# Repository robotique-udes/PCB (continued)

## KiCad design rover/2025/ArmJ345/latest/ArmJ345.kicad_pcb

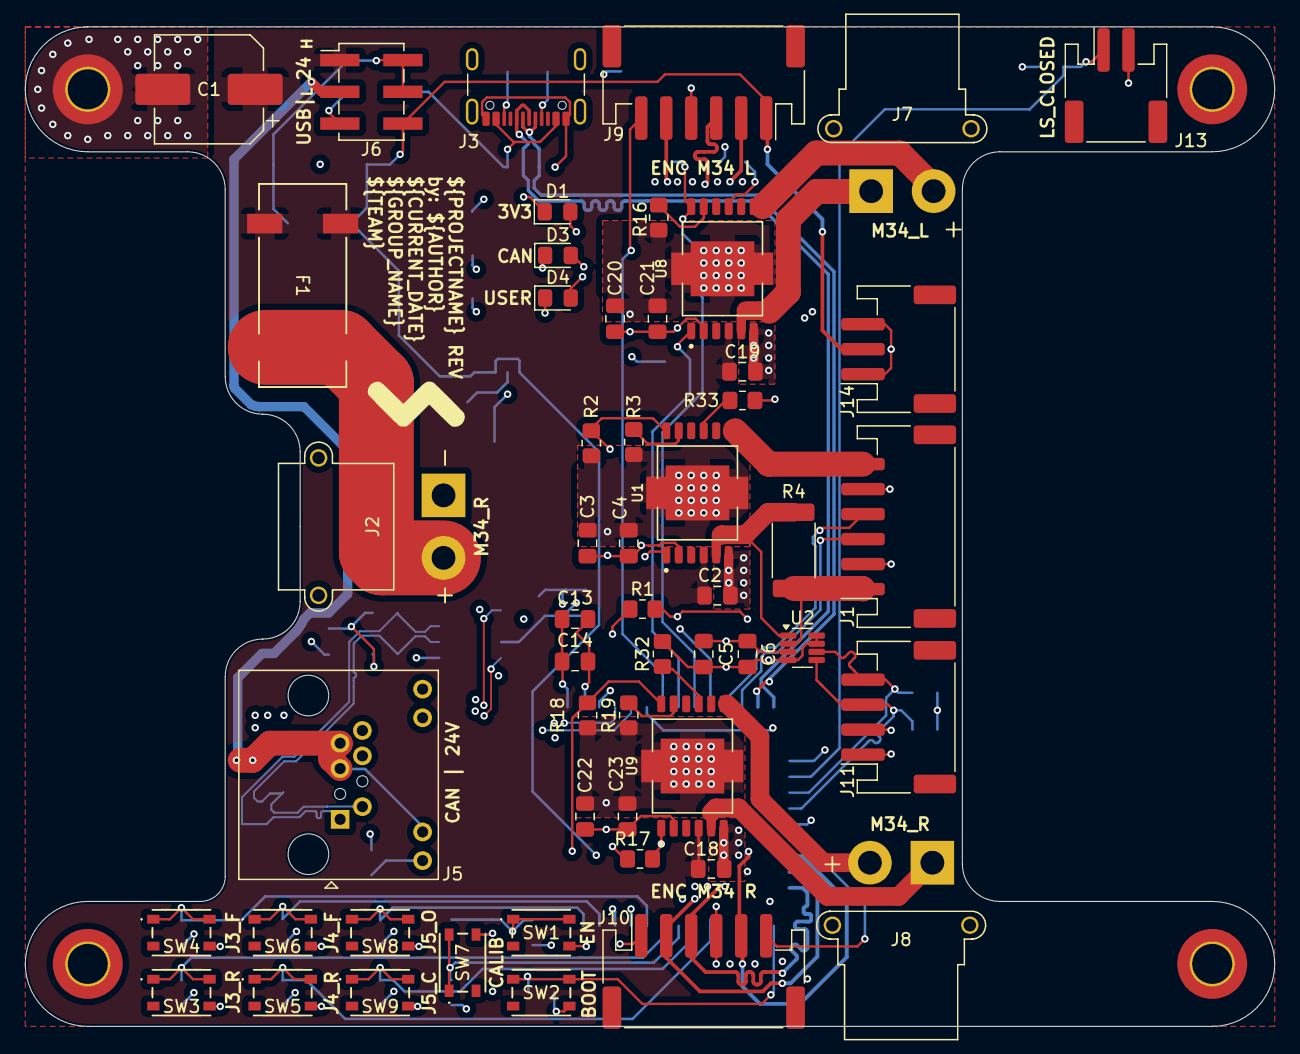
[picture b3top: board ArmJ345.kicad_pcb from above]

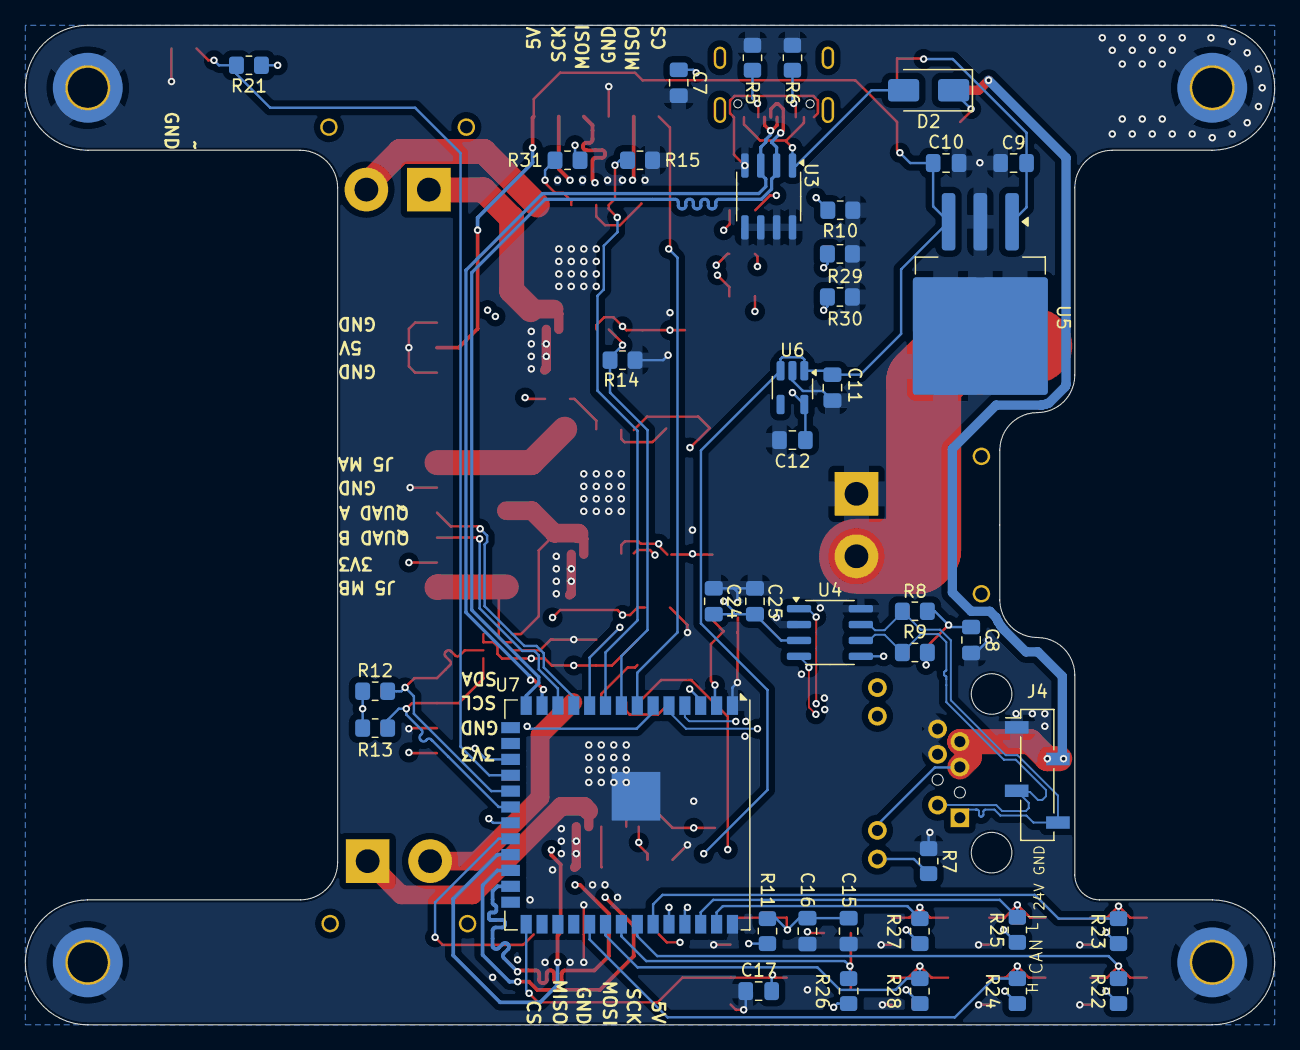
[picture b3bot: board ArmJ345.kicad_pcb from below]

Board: 4 copper layers, 100.0 x 80.0 mm, 97 parts (40 on the bottom side), 63 nets.

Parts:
C1: 470uF; CP_Elec_8x10.5
C2, C4, C6, C14, C16, C17, C18, C19, C21, C23, C25: 100nF; C_0805_2012Metric_Pad1.18x1.45mm_HandSolder
C3, C5, C9, C10, C11, C12, C13, C20, C22, C24: 10uF; C_0805_2012Metric_Pad1.18x1.45mm_HandSolder
C7: 1nF; C_0805_2012Metric_Pad1.18x1.45mm_HandSolder
C8: 4.7nF; C_0805_2012Metric_Pad1.18x1.45mm_HandSolder
C15: 1uF; C_0805_2012Metric_Pad1.18x1.45mm_HandSolder
D1: G; LED_0805_2012Metric_Pad1.15x1.40mm_HandSolder
D2: 40V; D_SMA
D3, D4: B; LED_0805_2012Metric_Pad1.15x1.40mm_HandSolder
F1: 15A; FuseHolder-3588-20
H1, H2, H3, H4: MountingHole_Pad; MountingHole_3.2mm_M3_DIN965_Pad_TopBottom
J1: JST_PH_SB6; JST_PH_S6B-PH-SM4-TB_1x06-1MP_P2.00mm_Horizontal
J2: XT30PW-M; AMASS_XT30PW-M_1x02_P2.50mm_Horizontal
J3: USB_C_USB4105-GF-A; USB_C_Receptacle_GCT_USB4105-xx-A_16P_TopMnt_Horizontal
J4: Conn_01x04_Socket; PinSocket_1x04_P2.54mm_Vertical_SMD_Pin1Left
J5: ETH-RJHSE5081
J6: Conn_02x03_Odd_Even; PinHeader_2x03_P2.54mm_Vertical_SMD
J7, J8: XT30PW-M; AMASS_XT30PW-F_1x02_P2.50mm_Horizontal
J9, J10: JST-PH-S6B; JST_PH_S6B-PH-SM4-TB_1x06-1MP_P2.00mm_Horizontal
J11: Conn_01x04_MountingPin; JST_PH_S4B-PH-SM4-TB_1x04-1MP_P2.00mm_Horizontal
J13: Conn_01x02_MountingPin; JST_PH_S2B-PH-SM4-TB_1x02-1MP_P2.00mm_Horizontal
J14: Conn_01x03_MountingPin; JST_PH_S3B-PH-SM4-TB_1x03-1MP_P2.00mm_Horizontal
R1, R2, R3, R11, R14, R15, R16, R17, R18, R19, R21, R22, R23, R24, R25, R26, R27, R28, R31, R32, R33: 10k; R_0805_2012Metric_Pad1.20x1.40mm_HandSolder
R4: 0.05 (CRA2512-FZ-R050ELF); R_2512_6332Metric_Pad1.40x3.35mm_HandSolder
R5, R6, R7, R10, R29, R30: 5.1k; R_0805_2012Metric_Pad1.20x1.40mm_HandSolder
R8, R9: 60.4; R_0805_2012Metric_Pad1.20x1.40mm_HandSolder
R12, R13: 4.7k; R_0805_2012Metric_Pad1.20x1.40mm_HandSolder
SW1, SW2, SW3, SW4, SW5, SW6, SW7, SW8, SW9: SW-PTS815SJM250SMTRLFS; SW-PTS815 SJM250SMTRLFS
U1, U8, U9: IFX9201SGAUMA1; DRIVE_IFX9201SGAUMA1
U2: CURR_SENSE-INA219AIDCNTG4; SOT-23-8
U3: TVS-SMDB03CE3; SOIC-8_3.9x4.9mm_P1.27mm
U4: SN65HVD232; SOIC-8_3.9x4.9mm_P1.27mm
U5: LDO-LM340SX-5.0/NOPB; TO-263-3_TabPin2
U6: LDO-TLV74033PDBVR; SOT-23-5_HandSoldering
U7: ESP32-S3-WROVER; ESP32-S3-WROOM-1U

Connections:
+3.3V: C3.1, C4.1, C5.1, C6.1, C12.1, C13.1, C14.1, C20.1, C21.1, C22.1, C23.1, C24.1, C25.1, D1.2 (A), J1.2, J11.1, R11.1, R12.1, R13.1, R21.1, R22.1, R23.1, R24.1, R25.1, R26.1, R27.1, R28.1, R31.1, R32.1, R33.1, U1.2 (VSO), U2.4 (VS), U2.7 (A0), U2.8 (A1), U4.3 (VCC), U4.5 (VREF), U6.5 (OUTPUT), U7.2 (3V3), U8.2 (VSO), U9.2 (VSO)
+5V: C10.1, C11.1, J6.6, J9.1, J10.1, J14.2, U5.3 (OUTPUT), U6.1 (INPUT), U6.3 (EN)
+5V_USB: D2.2 (A), J3.A4 (VBUS), J3.A9 (VBUS), J3.B4 (VBUS), J3.B9 (VBUS), U3.1
+24V: C9.1, J6.2, J6.4, U5.1 (INPUT)
+24V_H: C1.1, C2.1, C18.1, C19.1, F1.1, J6.1, U1.4 (VS), U8.4 (VS), U9.4 (VS)
+24V_L: J4.2, J5.5 (Vcc), J5.7 (Vcc), J5.10 (G_L+), J6.3
/Board/drive_j5/M5_A: J1.6, U1.7 (OUT2)
/Board/drive_j5/M5_B: J1.1, R4.2, U2.2 (IN-)
/Board/drive_j5/SENSE_+: R4.1, U1.5 (OUT1), U2.1 (IN+)
/Board/esp32/BOOT_PB: C17.2, SW2.1, SW2.2, U7.27 (IO0-BOOT)
/Board/esp32/CAN_LED: D3.2 (A), U7.17 (IO9)
/Board/esp32/EN_PB: C15.1, C16.2, R11.2, SW1.1, SW1.2, U7.3 (EN)
/Board/esp32/USER_LED: D4.2 (A), U7.6 (IO6)
/Board/external_connections/CC1: J3.A5 (CC1), R5.1
/Board/external_connections/CC2: J3.B5 (CC2), R6.1
CAN_N: J4.3, J5.2 (CANL), R9.1, U4.6 (CANL)
CAN_P: J4.4, J5.1 (CANH), R8.2, U4.7 (CANH)
CAN_RX: U4.4 (RXD), U7.5 (IO5)
CAN_TX: U4.1 (TXD), U7.4 (IO4)
GND: C1.2, C2.2, C3.2, C4.2, C5.2, C6.2, C7.2, C8.2, C9.2, C10.2, C11.2, C12.2, C13.2, C14.2, C15.2, C16.1, C17.1, C18.2, C19.2, C20.2, C21.2, C22.2, C23.2, C24.2, C25.2, H1.1, H2.1, H3.1, H4.1, J1.5, J2.1 (-), J3.A1 (GND), J3.A12 (GND), J3.B1 (GND), J3.B12 (GND), J4.1, J5.6 (GND), J5.8 (GND), J9.4, J10.4, J11.2, J13.2, J14.1, J14.3, R1.2, R2.2, R3.2, R5.2, R6.2, R7.1, R10.1, R14.2, R15.2, R16.2, R17.2, R18.2, R19.2, R29.1, R30.1, SW1.4, SW2.4, SW3.4, SW4.4, SW5.4, SW6.4, SW7.4, SW8.4, SW9.4, U1.6 (GND), U2.3 (GND), U3.4, U3.5, U3.6, U3.7, U3.8, U4.2 (GND), U4.8 (S), U5.2 (GND), U6.2 (GND), U7.1 (GND), U7.40 (GND), U7.41 (GND), U8.6 (GND), U9.6 (GND)
I2C_SCL: J11.3, R13.2, U2.5 (SCL), U7.20 (IO12)
I2C_SDA: J11.4, R12.2, U2.6 (SDA), U7.19 (IO11)
J5_DIR: R1.1, U1.1 (DIR), U7.21 (IO13)
J5_PWM: R2.1, U1.12 (PWM), U7.10 (IO17)
J5_QUAD_A: J1.4, U7.11 (IO18)
J5_QUAD_B: J1.3, U7.12 (IO8)
J34_L_DIR: R14.1, U7.8 (IO15), U8.1 (DIR)
J34_L_PWM: R15.1, U7.9 (IO16), U8.12 (PWM)
J34_R_DIR: R17.1, U7.36 (RXD0), U9.1 (DIR)
J34_R_PWM: R18.1, U7.37 (TXD0), U9.12 (PWM)
M5_LS_CLOSED: J13.1, R21.2, U7.18 (IO10)
unnamed: C8.1, R8.1, R9.2
unnamed: D1.1 (K), R10.2
unnamed: D2.1 (K), J6.5
unnamed: D3.1 (K), R29.2
unnamed: D4.1 (K), R30.2
unnamed: F1.2, J2.2 (+)
unnamed: C7.1, J3.S1 (SHIELD)
unnamed: J5.9 (G_L-), R7.2
unnamed: J7.2 (+), U8.7 (OUT2)
unnamed: J7.1 (-), U8.5 (OUT1)
unnamed: J8.2 (+), U9.7 (OUT2)
unnamed: J8.1 (-), U9.5 (OUT1)
unnamed: R33.2, U1.9 (~CS)
unnamed: R3.1, U1.11 (~EN(DIS))
unnamed: R31.2, U8.9 (~CS)
unnamed: R16.1, U8.11 (~EN(DIS))
unnamed: R32.2, U9.9 (~CS)
unnamed: R19.1, U9.11 (~EN(DIS))
PB_J3_FWD: R23.2, SW4.1, SW4.2, U7.35 (IO42)
PB_J3_REV: R22.2, SW3.1, SW3.2, U7.34 (IO41)
PB_J4_FWD: R25.2, SW6.1, SW6.2, U7.38 (IO2)
PB_J4_REV: R24.2, SW5.1, SW5.2, U7.31 (IO38)
PB_J5_CLOSE: R28.2, SW9.1, SW9.2, U7.32 (IO39)
PB_J5_OPEN: R27.2, SW8.1, SW8.2, U7.39 (IO1)
PB_J34_CALIB: R26.2, SW7.1, SW7.2, U7.33 (IO40)
SPI_CS_ENC_L: J9.6, U7.7 (IO7)
SPI_CS_ENC_R: J10.6, U7.22 (IO14)
SPI_MISO: J9.5, J10.5, U7.23 (IO21)
SPI_MOSI: J9.3, J10.3, U7.25 (IO48)
SPI_SCK: J9.2, J10.2, U7.24 (IO47)
USB_N: J3.A7 (D-), J3.B7 (D-), U3.3, U7.13 (IO19-USB_N)
USB_P: J3.A6 (D+), J3.B6 (D+), U3.2, U7.14 (IO20-USB-P)

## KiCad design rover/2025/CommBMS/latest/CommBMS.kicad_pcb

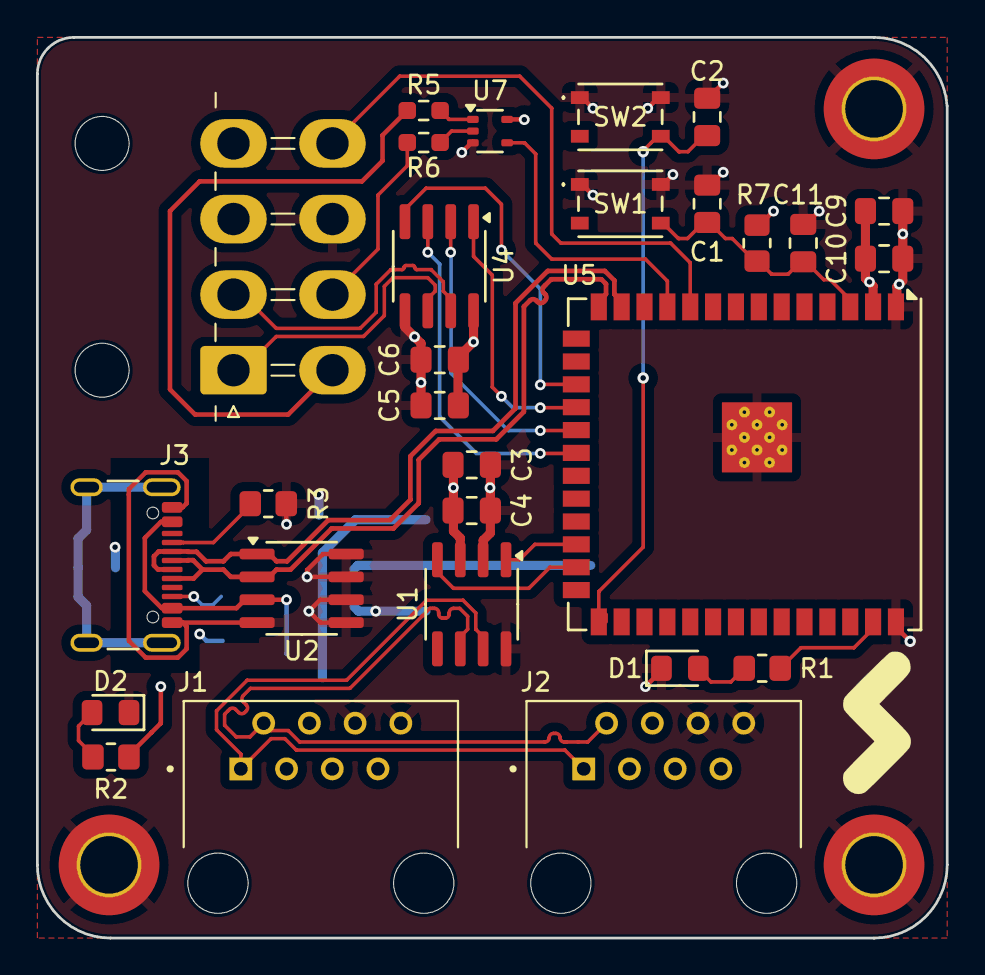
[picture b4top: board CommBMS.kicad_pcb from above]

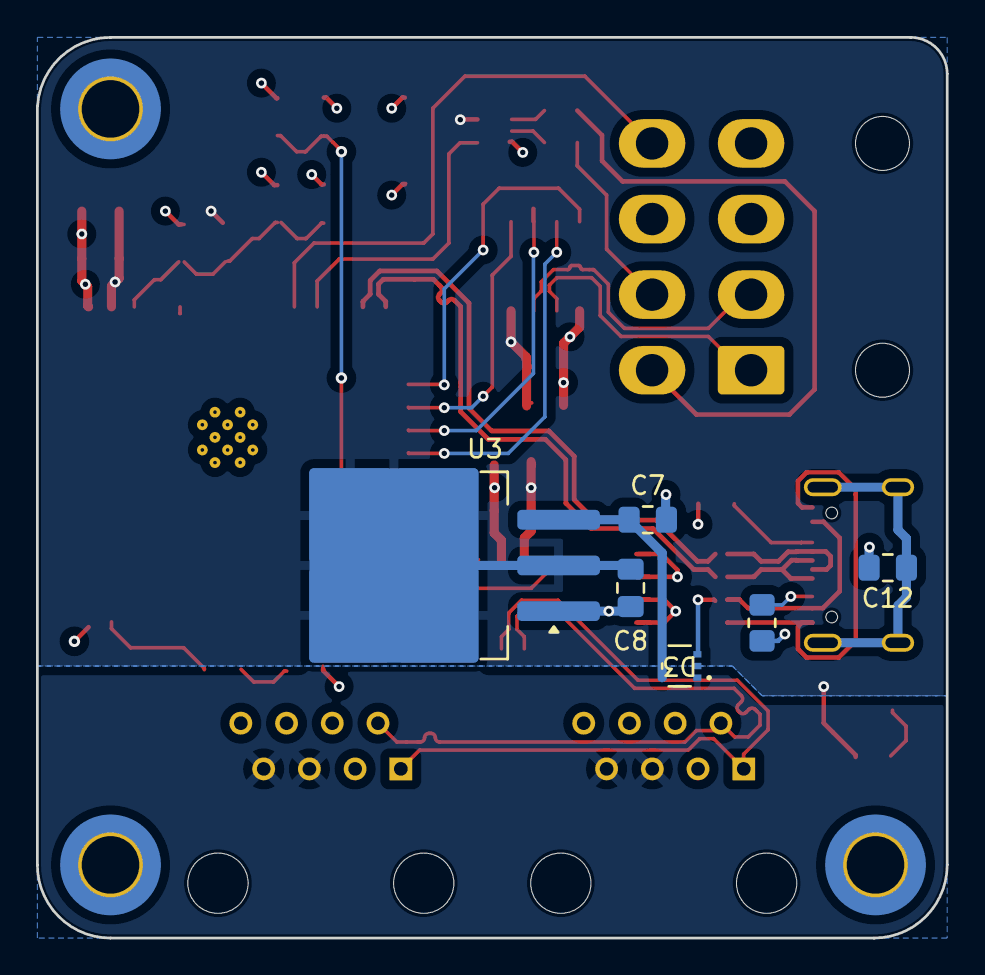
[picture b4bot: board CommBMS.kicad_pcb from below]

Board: 4 copper layers, 50.5 x 50.0 mm, 37 parts (6 on the bottom side), 31 nets.

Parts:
C1, C2, C4, C6, C10: 100nF; C_0805_2012Metric_Pad1.18x1.45mm_HandSolder
C3, C5, C7, C8, C9: 10uF; C_0805_2012Metric_Pad1.18x1.45mm_HandSolder
C11: 1uF; C_0805_2012Metric_Pad1.18x1.45mm_HandSolder
C12: 1n; C_0805_2012Metric_Pad1.18x1.45mm_HandSolder
D1: R; LED_0805_2012Metric_Pad1.15x1.40mm_HandSolder
D2: G; LED_0805_2012Metric_Pad1.15x1.40mm_HandSolder
D3: CVJ10F30; Diode_schottky-CVJ10F30
H1, H2, H3: MountingHole_Pad; MountingHole_3.2mm_M3_DIN965_Pad_TopBottom
J1, J2: Eth-Horiz-54601-908WPLF; Ethernet_Horizontal
J3: USB_C_USB4105-GF-A; USB_C_Receptacle_GCT_USB4105-xx-A_16P_TopMnt_Horizontal
J4: CONN-MOLEX_8PIN-39301080
R1, R2: 1k; R_0805_2012Metric_Pad1.20x1.40mm_HandSolder
R3, R4: 5k1; R_0805_2012Metric_Pad1.20x1.40mm_HandSolder
R5, R6: 0; R_0603_1608Metric_Pad0.98x0.95mm_HandSolder
R7: 10k; R_0805_2012Metric_Pad1.20x1.40mm_HandSolder
SW1, SW2: TS09-63-25-WT-160-SMT-TR; SW-PTS815 SJM250SMTRLFS
U1: SN65HVD232Q; SOIC-8_3.9x4.9mm_P1.27mm
U2: TVS; SOIC-8_3.9x4.9mm_P1.27mm
U3: LDO-LM7805MPX/NOPB; TO-263-3_TabPin2
U4: SP3485EN; SOIC-8_3.9x4.9mm_P1.27mm
U5: ESP32-S3-WROOM-1; ESP32-S3-WROOM-1U
U7: AXP1T34; SOT-353_SC-70-5

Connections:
+3.3V: C3.1, C4.1, C5.1, C6.1, C8.1, C9.1, C10.1, R2.2, R7.1, U1.3 (VCC), U3.2 (OUTPUT), U4.8 (VCC), U5.2 (3V3), U7.5 (Vcco)
+5V_BMS: J4.5, R5.1
+5V_USB: D3.3, J3.A4 (VBUS), J3.A9 (VBUS), J3.B4 (VBUS), J3.B9 (VBUS), U2.3
+24V_ETH: D3.1, J1.5, J1.7, J2.5, J2.7
BMS_A: J4.1, U4.6 (A)
BMS_B: J4.2, U4.7 (B)
CANH: J1.1 (CANH), J2.1 (CANH), U1.7 (CANH)
CANL: J1.2 (CANL), J2.2 (CANL), U1.6 (CANL)
DE: U4.3 (DE), U5.20 (IO12)
DIN2: J4.8, U5.10 (IO17)
EN_PB: C1.2, C11.1, R7.2, SW1.4, U5.3 (EN)
GND: C1.1, C2.1, C3.2, C4.2, C5.2, C6.2, C7.2, C8.2, C9.2, C10.2, C11.2, C12.2, D1.1 (K), D2.1 (K), H1.1, H2.1, H3.1, J1.6, J1.8, J2.6, J2.8, J3.A1 (GND), J3.A12 (GND), J3.B1 (GND), J3.B12 (GND), J4.7, R3.2, R4.2, SW1.1, SW1.2, SW2.1, SW2.2, U1.2 (GND), U1.8 (S), U2.4, U2.5, U2.6, U2.7, U2.8, U3.1 (GND), U4.5 (GND), U5.1 (GND), U5.40 (GND), U5.41 (GND), U7.3 (GND)
GPIO_0: C2.2, SW2.4, U5.27 (IO0-BOOT)
LED_BUILDIN: R1.2, U5.39 (IO1)
unnamed: D1.2 (A), R1.1
unnamed: D2.2 (A), R2.1
unnamed: J3.A5 (CC1), R3.1
unnamed: J3.B5 (CC2), R4.1
unnamed: C12.1, J3.S1 (SHIELD)
unnamed: C7.1, D3.4, D3.5, U3.3 (INPUT)
unnamed: R6.2, U7.2 (INPUT)
unnamed: R5.2, U7.1 (Vcci)
PWM_3V: U5.11 (IO18), U7.4 (OUTPUT)
PWM_5V: J4.6, R6.1
RE: U4.2 (RE), U5.19 (IO11)
RXB: U4.1 (RXD), U5.18 (IO10)
RXC: U1.4 (RXD), U5.25 (IO48)
TXB: U4.4 (TXD), U5.17 (IO9)
TXC: U1.1 (TXD), U5.24 (IO47)
USB_N: J3.A7 (D-), J3.B7 (D-), U2.1, U5.13 (IO19-USB_N)
USB_P: J3.A6 (D+), J3.B6 (D+), U2.2, U5.14 (IO20-USB-P)

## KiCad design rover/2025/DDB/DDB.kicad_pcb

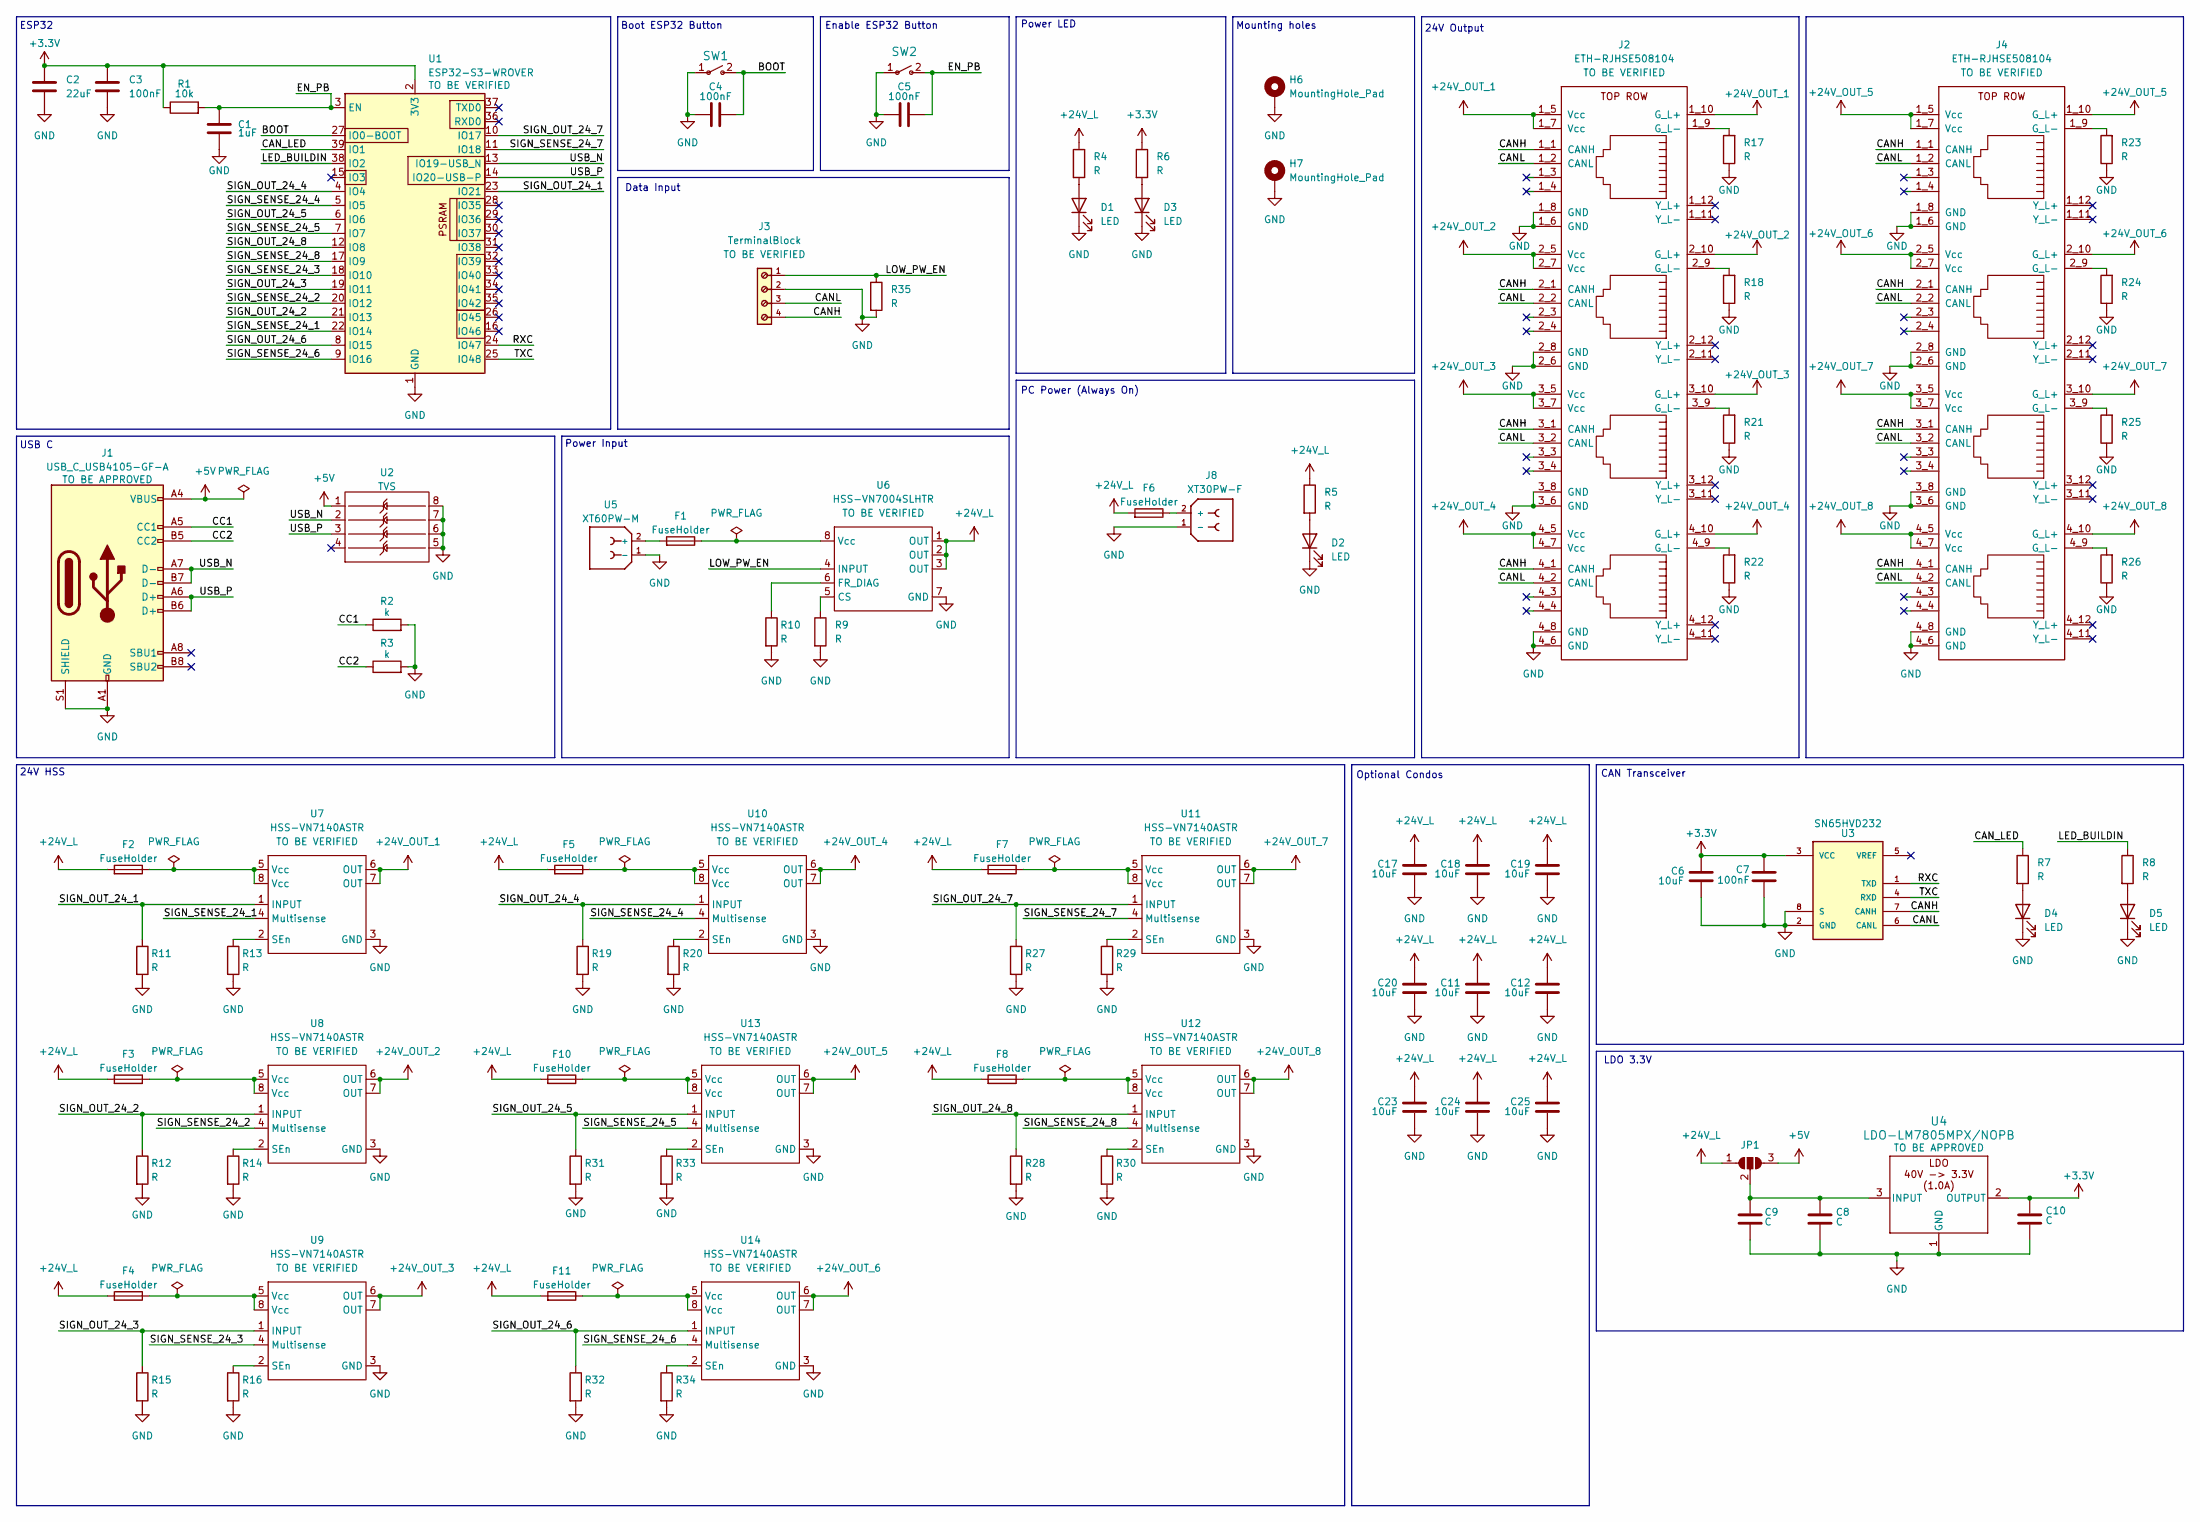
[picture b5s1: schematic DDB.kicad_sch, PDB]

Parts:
C1: 1uF; C_0805_2012Metric_Pad1.18x1.45mm_HandSolder
C2: 22uF; C_0805_2012Metric_Pad1.18x1.45mm_HandSolder
C3, C4, C5, C7: 100nF; C_0805_2012Metric_Pad1.18x1.45mm_HandSolder
C6, C11, C12, C17, C18, C19, C20, C23, C24, C25: 10uF; C_0805_2012Metric_Pad1.18x1.45mm_HandSolder
C8, C9, C10: C; LED_0805_2012Metric
D1, D2, D3, D4, D5: LED; D_0805_2012Metric_Pad1.15x1.40mm_HandSolder
F1, F2, F3, F4, F5, F6, F7, F8, F10, F11: FuseHolder; FUSE_3568-20
H6, H7: MountingHole_Pad; MountingHole_3.2mm_M3_DIN965_Pad_TopBottom
J1: USB_C_USB4105-GF-A; USB_C_Receptacle_GCT_USB4105-xx-A_16P_TopMnt_Horizontal
J2, J4: ETH-RJHSE508104
J3: TerminalBlock; TerminalBlock-4_P5.00mm-691137710004; PART-NUMBER 691137710004
J8: XT30PW-F; AMASS_XT30PW-F_1x02_P2.50mm_Horizontal; PARTREV 1.2
JP1: SolderJumper_3_Open; PinHeader_1x03_P2.54mm_Vertical
R1: 10k; R_0805_2012Metric_Pad1.20x1.40mm_HandSolder
R2, R3: k; R_0805_2012Metric_Pad1.20x1.40mm_HandSolder
R4, R5, R6, R7, R8, R9, R10, R11, R12, R13, R14, R15, R16, R17, R18, R19, R20, R21, R22, R23, R24, R25, R26, R27, R28, R29, R30, R31, R32, R33, R34, R35: R; R_0805_2012Metric_Pad1.20x1.40mm_HandSolder
SW1, SW2: TS09-63-25-WT-160-SMT-TR; SW_DIP_SPSTx01_Slide_6.7x4.1mm_W8.61mm_P2.54mm_LowProfile
U1: ESP32-S3-WROVER; ESP32-S3-WROOM-1U
U2: TVS; SOIC-8_3.9x4.9mm_P1.27mm
U3: SN65HVD232; SOIC-8_3.9x4.9mm_P1.27mm; PARTREV 4
U4: LDO-LM7805MPX/NOPB; TO-252-2
U5: XT60PW-M; AMASS_XT60PW-M_1x02_P7.20mm_Horizontal
U6: HSS-VN7004SLHTR; OCTAPACK_VN7004_STM-M
U7, U8, U9, U10, U11, U12, U13, U14: HSS-VN7140ASTR; SOIC-8_3.9x4.9mm_P1.27mm

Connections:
+3.3V: C2.1, C3.1, C6.1, C7.1, C10.1, R1.1, R6.1, U1.2 (3V3), U3.3 (VCC), U4.2 (OUTPUT)
+5V: J1.A4 (VBUS), J1.A9 (VBUS), J1.B4 (VBUS), J1.B9 (VBUS), JP1.3 (B), U2.1
+24V_L: C11.1, C12.1, C17.1, C18.1, C19.1, C20.1, C23.1, C24.1, C25.1, F2.1, F3.1, F4.1, F5.1, F6.1, F7.1, F8.1, F10.1, F11.1, JP1.1 (A), R4.1, R5.1, U6.1 (OUT), U6.2 (OUT), U6.3 (OUT)
+24V_OUT_1: J2.1_5 (Vcc), J2.1_7 (Vcc), J2.1_10 (G_L+), U7.6 (OUT), U7.7 (OUT)
+24V_OUT_2: J2.2_5 (Vcc), J2.2_7 (Vcc), J2.2_10 (G_L+), U8.6 (OUT), U8.7 (OUT)
+24V_OUT_3: J2.3_5 (Vcc), J2.3_7 (Vcc), J2.3_10 (G_L+), U9.6 (OUT), U9.7 (OUT)
+24V_OUT_4: J2.4_5 (Vcc), J2.4_7 (Vcc), J2.4_10 (G_L+), U10.6 (OUT), U10.7 (OUT)
+24V_OUT_5: J4.1_5 (Vcc), J4.1_7 (Vcc), J4.1_10 (G_L+), U13.6 (OUT), U13.7 (OUT)
+24V_OUT_6: J4.2_5 (Vcc), J4.2_7 (Vcc), J4.2_10 (G_L+), U14.6 (OUT), U14.7 (OUT)
+24V_OUT_7: J4.3_5 (Vcc), J4.3_7 (Vcc), J4.3_10 (G_L+), U11.6 (OUT), U11.7 (OUT)
+24V_OUT_8: J4.4_5 (Vcc), J4.4_7 (Vcc), J4.4_10 (G_L+), U12.6 (OUT), U12.7 (OUT)
/BOOT: C4.2, SW1.2, U1.27 (IO0-BOOT)
/CANH: J2.1_1 (CANH), J2.2_1 (CANH), J2.3_1 (CANH), J2.4_1 (CANH), J3.4, J4.1_1 (CANH), J4.2_1 (CANH), J4.3_1 (CANH), J4.4_1 (CANH), U3.7 (CANH)
/CANL: J2.1_2 (CANL), J2.2_2 (CANL), J2.3_2 (CANL), J2.4_2 (CANL), J3.3, J4.1_2 (CANL), J4.2_2 (CANL), J4.3_2 (CANL), J4.4_2 (CANL), U3.6 (CANL)
/CAN_LED: R7.1, U1.39 (IO1)
/CC1: J1.A5 (CC1), R2.1
/CC2: J1.B5 (CC2), R3.1
/EN_PB: C1.1, C5.2, R1.2, SW2.2, U1.3 (EN)
/LED_BUILDIN: R8.1, U1.38 (IO2)
/LOW_PW_EN: J3.1, R35.1, U6.4 (INPUT)
/RXC: U1.24 (IO47), U3.1 (TXD)
/SIGN_OUT_24_1: R11.1, U1.23 (IO21), U7.1 (INPUT)
/SIGN_OUT_24_2: R12.1, U1.21 (IO13), U8.1 (INPUT)
/SIGN_OUT_24_3: R15.1, U1.19 (IO11), U9.1 (INPUT)
/SIGN_OUT_24_4: R19.1, U1.4 (IO4), U10.1 (INPUT)
/SIGN_OUT_24_5: R31.1, U1.6 (IO6), U13.1 (INPUT)
/SIGN_OUT_24_6: R32.1, U1.8 (IO15), U14.1 (INPUT)
/SIGN_OUT_24_7: R27.1, U1.10 (IO17), U11.1 (INPUT)
/SIGN_OUT_24_8: R28.1, U1.12 (IO8), U12.1 (INPUT)
/SIGN_SENSE_24_1: U1.22 (IO14), U7.4 (Multisense)
/SIGN_SENSE_24_2: U1.20 (IO12), U8.4 (Multisense)
/SIGN_SENSE_24_3: U1.18 (IO10), U9.4 (Multisense)
/SIGN_SENSE_24_4: U1.5 (IO5), U10.4 (Multisense)
/SIGN_SENSE_24_5: U1.7 (IO7), U13.4 (Multisense)
/SIGN_SENSE_24_6: U1.9 (IO16), U14.4 (Multisense)
/SIGN_SENSE_24_7: U1.11 (IO18), U11.4 (Multisense)
/SIGN_SENSE_24_8: U1.17 (IO9), U12.4 (Multisense)
/TXC: U1.25 (IO48), U3.4 (RXD)
/USB_N: J1.A7 (D-), J1.B7 (D-), U1.13 (IO19-USB_N), U2.2
/USB_P: J1.A6 (D+), J1.B6 (D+), U1.14 (IO20-USB-P), U2.3
GND: C1.2, C2.2, C3.2, C4.1, C5.1, C6.2, C7.2, C8.2, C9.2, C10.2, C11.2, C12.2, C17.2, C18.2, C19.2, C20.2, C23.2, C24.2, C25.2, D1.1 (K), D2.1 (K), D3.1 (K), D4.1 (K), D5.1 (K), H6.1, H7.1, J1.A1 (GND), J1.A12 (GND), J1.B1 (GND), J1.B12 (GND), J1.S1 (SHIELD), J2.1_6 (GND), J2.1_8 (GND), J2.2_6 (GND), J2.2_8 (GND), J2.3_6 (GND), J2.3_8 (GND), J2.4_6 (GND), J2.4_8 (GND), J3.2, J4.1_6 (GND), J4.1_8 (GND), J4.2_6 (GND), J4.2_8 (GND), J4.3_6 (GND), J4.3_8 (GND), J4.4_6 (GND), J4.4_8 (GND), J8.1 (-), R2.2, R3.2, R9.2, R10.2, R11.2, R12.2, R13.2, R14.2, R15.2, R16.2, R17.1, R18.1, R19.2, R20.2, R21.1, R22.1, R23.1, R24.1, R25.1, R26.1, R27.2, R28.2, R29.2, R30.2, R31.2, R32.2, R33.2, R34.2, R35.2, SW1.1, SW2.1, U1.1 (GND), U1.40 (GND), U1.41 (GND), U2.5, U2.6, U2.7, U2.8, U3.2 (GND), U3.8 (S), U4.1 (GND), U5.1 (-), U6.7 (GND), U7.3 (GND), U8.3 (GND), U9.3 (GND), U10.3 (GND), U11.3 (GND), U12.3 (GND), U13.3 (GND), U14.3 (GND)
unnamed: D1.2 (A), R4.2
unnamed: D2.2 (A), R5.2
unnamed: D3.2 (A), R6.2
unnamed: D4.2 (A), R7.2
unnamed: D5.2 (A), R8.2
unnamed: F2.2, U7.5 (Vcc), U7.8 (Vcc)
unnamed: F3.2, U8.5 (Vcc), U8.8 (Vcc)
unnamed: F4.2, U9.5 (Vcc), U9.8 (Vcc)
unnamed: F5.2, U10.5 (Vcc), U10.8 (Vcc)
unnamed: F7.2, U11.5 (Vcc), U11.8 (Vcc)
unnamed: F8.2, U12.5 (Vcc), U12.8 (Vcc)
unnamed: F10.2, U13.5 (Vcc), U13.8 (Vcc)
unnamed: F11.2, U14.5 (Vcc), U14.8 (Vcc)
unnamed: J2.1_9 (G_L-), R17.2
unnamed: J2.2_9 (G_L-), R18.2
unnamed: J2.3_9 (G_L-), R21.2
unnamed: J2.4_9 (G_L-), R22.2
unnamed: J4.1_9 (G_L-), R23.2
unnamed: J4.2_9 (G_L-), R24.2
unnamed: J4.3_9 (G_L-), R25.2
unnamed: J4.4_9 (G_L-), R26.2
unnamed: F6.2, J8.2 (+)
unnamed: C8.1, C9.1, JP1.2 (C), U4.3 (INPUT)
unnamed: F1.1, U5.2 (+)
unnamed: R9.1, U6.5 (CS)
unnamed: R10.1, U6.6 (FR_DIAG)
unnamed: F1.2, U6.8 (Vcc)
unnamed: R13.1, U7.2 (SEn)
unnamed: R14.1, U8.2 (SEn)
unnamed: R16.1, U9.2 (SEn)
unnamed: R20.1, U10.2 (SEn)
unnamed: R29.1, U11.2 (SEn)
unnamed: R30.1, U12.2 (SEn)
unnamed: R33.1, U13.2 (SEn)
unnamed: R34.1, U14.2 (SEn)

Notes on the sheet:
Boot ESP32 Button
Mounting holes
Data Input
ESP32
USB C
24V Output
CAN Transceiver
24V HSS
Power Input
Enable ESP32 Button
Power LED
LDO 3.3V
Optional Condos
PC Power (Always On)

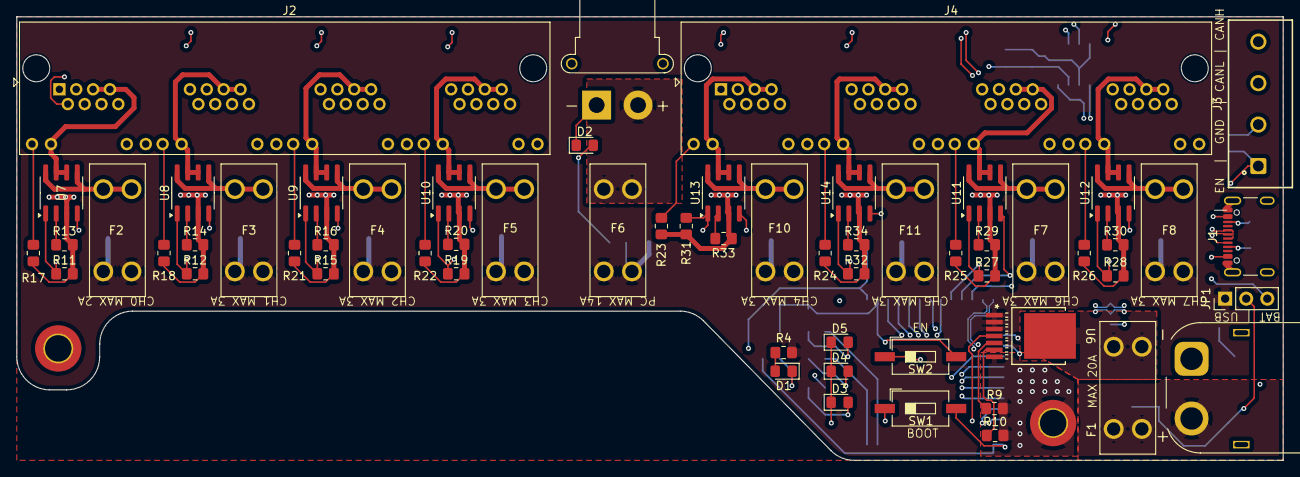
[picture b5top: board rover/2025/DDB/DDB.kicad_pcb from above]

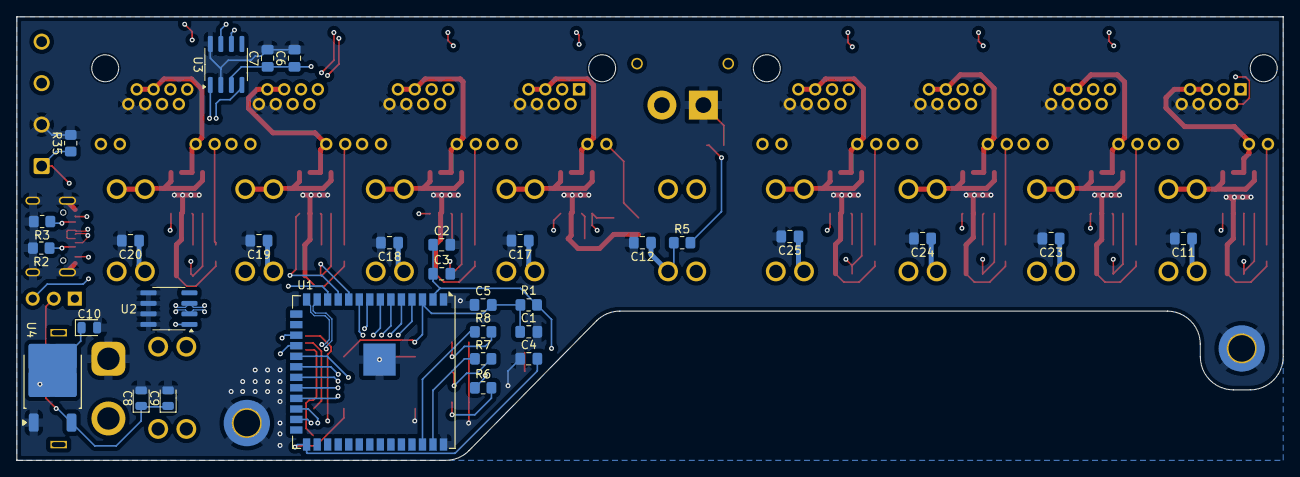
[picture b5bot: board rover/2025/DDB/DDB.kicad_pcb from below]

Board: 4 copper layers, 152.8 x 53.5 mm, 93 parts (31 on the bottom side), 76 nets.
